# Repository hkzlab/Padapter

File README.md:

# The Padapter, Genesis/MegaDrive gamepad to C64/Amiga adapter

## DISCLAIMER

Any use of this project is **under your own responsibility**.
You will be responsible of checking the correct construction and functionality of your board.
By using this project You will agree that I cannot be held responsible if it will destroy any of your devices, damage your computer, burn down your house or whatever.

## Introduction

This board converts a SEGA MegaDrive/Genesis 3-button gamepad for C64 (and similar)/Amiga use. It is inspired by the [OpenC64MegaDrivePadAdapter](https://github.com/SukkoPera/OpenC64MegaDrivePadAdapter).

All buttons on the gamepad are demultiplexed and usable by the computer, the adapter also provides two switchable mappings to help with games that used the joystick up direction for jumping.

### Ordering the boards

You can order the board for this project at [PCBWay](https://www.pcbway.com/project/shareproject/The_Padapter_6d3f13b7.html) and support me or download 
the gerbers and have them printed wherever you like!!!

Fabrication files are available for both PCBWay and JLCPCB inside the "gerbers" directory. Mind you that I have not yet tested assembly
of this board by either fab, as such you are on your own and you're invited to share your experience and improvements to these files.

## Features

- Small and made with common components
- Maps 3 buttons of the gamepad adapter, allowing their use on both C64 (and similar) and Amiga
- Two switchable button Maps

Amiga and C64 modes can be switched by moving JP1 and JP2:
- Pins 1-2 connected: Amiga Mode
- Pins 2-3 connected: C64 Mode

### Button Maps

Two button maps are available and switchable by flipping SW1 on the board.

They are switchable on the fly.

|              | Mode A   | Mode B   |
| ------------ | -------- | -------- |
| START        | Button 3 | Button 3 |
| A            | Button 3 | Button 2 |
| B            | Button 1 | Button 1 |
| C            | Button 2 | UP       |

## Hardware

The board was designed with [KiCad](https://kicad.org/) EDA.

### Bill of Materials

| Component              | Qty | Type / Value                                            | Notes                                                                |
| ---------------------- | --- | ------------------------------------------------------- | -------------------------------------------------------------------- |
| C1, C2                 |  2  | 10nF/10+V ceramic cap, SMD 0805                         |                                                                      |
| C3 - C15               | 13  | 100nF/10+V ceramic cap, SMD 0805                        |                                                                      |
| D1 - D5                |  5  | 1N4148W SOD-123F diode                                  |                                                                      |
| J1                     |  1  | DSUB-9 Female                                           | Connect toward C64/Amiga, use a connector with solder cups           |
| J2                     |  1  | DSUB-9 Male                                             | Connect toward MegaDrive pad, use a connector with solder cups       |
| JP1, JP2               |  2  | 3 pin 2.54mm headers                                    | Used to select between C64 and Amiga mode                            |
| Q1, Q2                 |  2  | BC847 SOT-23 transistors                                |                                                                      |
| R1, R3, R4, R6         |  4  | 2.2K ohm 0805 resistor                                  |                                                                      |
| R2, R5                 |  2  | 100K ohm 0805 resistor                                  |                                                                      |
| R7 - R9                |  3  | 10K ohm 0805 resistor                                   |                                                                      |
| RN1, RN2               |  2  | 10K resistor pack, 4x0612 (1206)                        |                                                                      |
| SW1                    |  1  | SPDT switch, C&K JS102011SAQN                           |                                                                      |
| U1                     |  1  | 74ACT08 TSSOP-14                                        |                                                                      |
| U2, U4                 |  2  | 74ACT373 SSOP-20                                        |                                                                      |
| U3                     |  1  | 74ACT157 TSSOP-16                                       |                                                                      |
| U5                     |  1  | 74AHC1G04 SOT-353 SC-70 5pin                            |                                                                      |
| 555                    |  1  | A CMOS 555 counter (e.g. LM555) SOIC-8                  |                                                                      |

### 💰 Selling these boards 💰

I you want to contact me about selling this project, you can reach me via email at `0hkzUNDERSCOREprojects6ATposteoDOTnet` after properly fixing the email address by removing the digits and replacing the uppercase words with the proper characters.

**Contacts via other channels will be ignored**, as it means you did not read this document thoroughly.

"Collaborations" will boil down to the following:

- If you wish to produce and share this project at a loss or at cost, go for it. I am only asking for attribution and to let me know via email.
- If you want to do it for profit, let's discuss it. I'll probably settle for a rough 5% of the profit. Importing components is getting more expensive by the day, so this will contribute to me making future projects available for free.
- I will NOT do customer assistance for you or your customers. This is a hobby, not my job.

If this is not ok for you, you're cordially invited to go bother someone else :)

Authorized sellers will be listed in this README. If you find someone selling my boards without being listed here, it means they're stealing other people's work.

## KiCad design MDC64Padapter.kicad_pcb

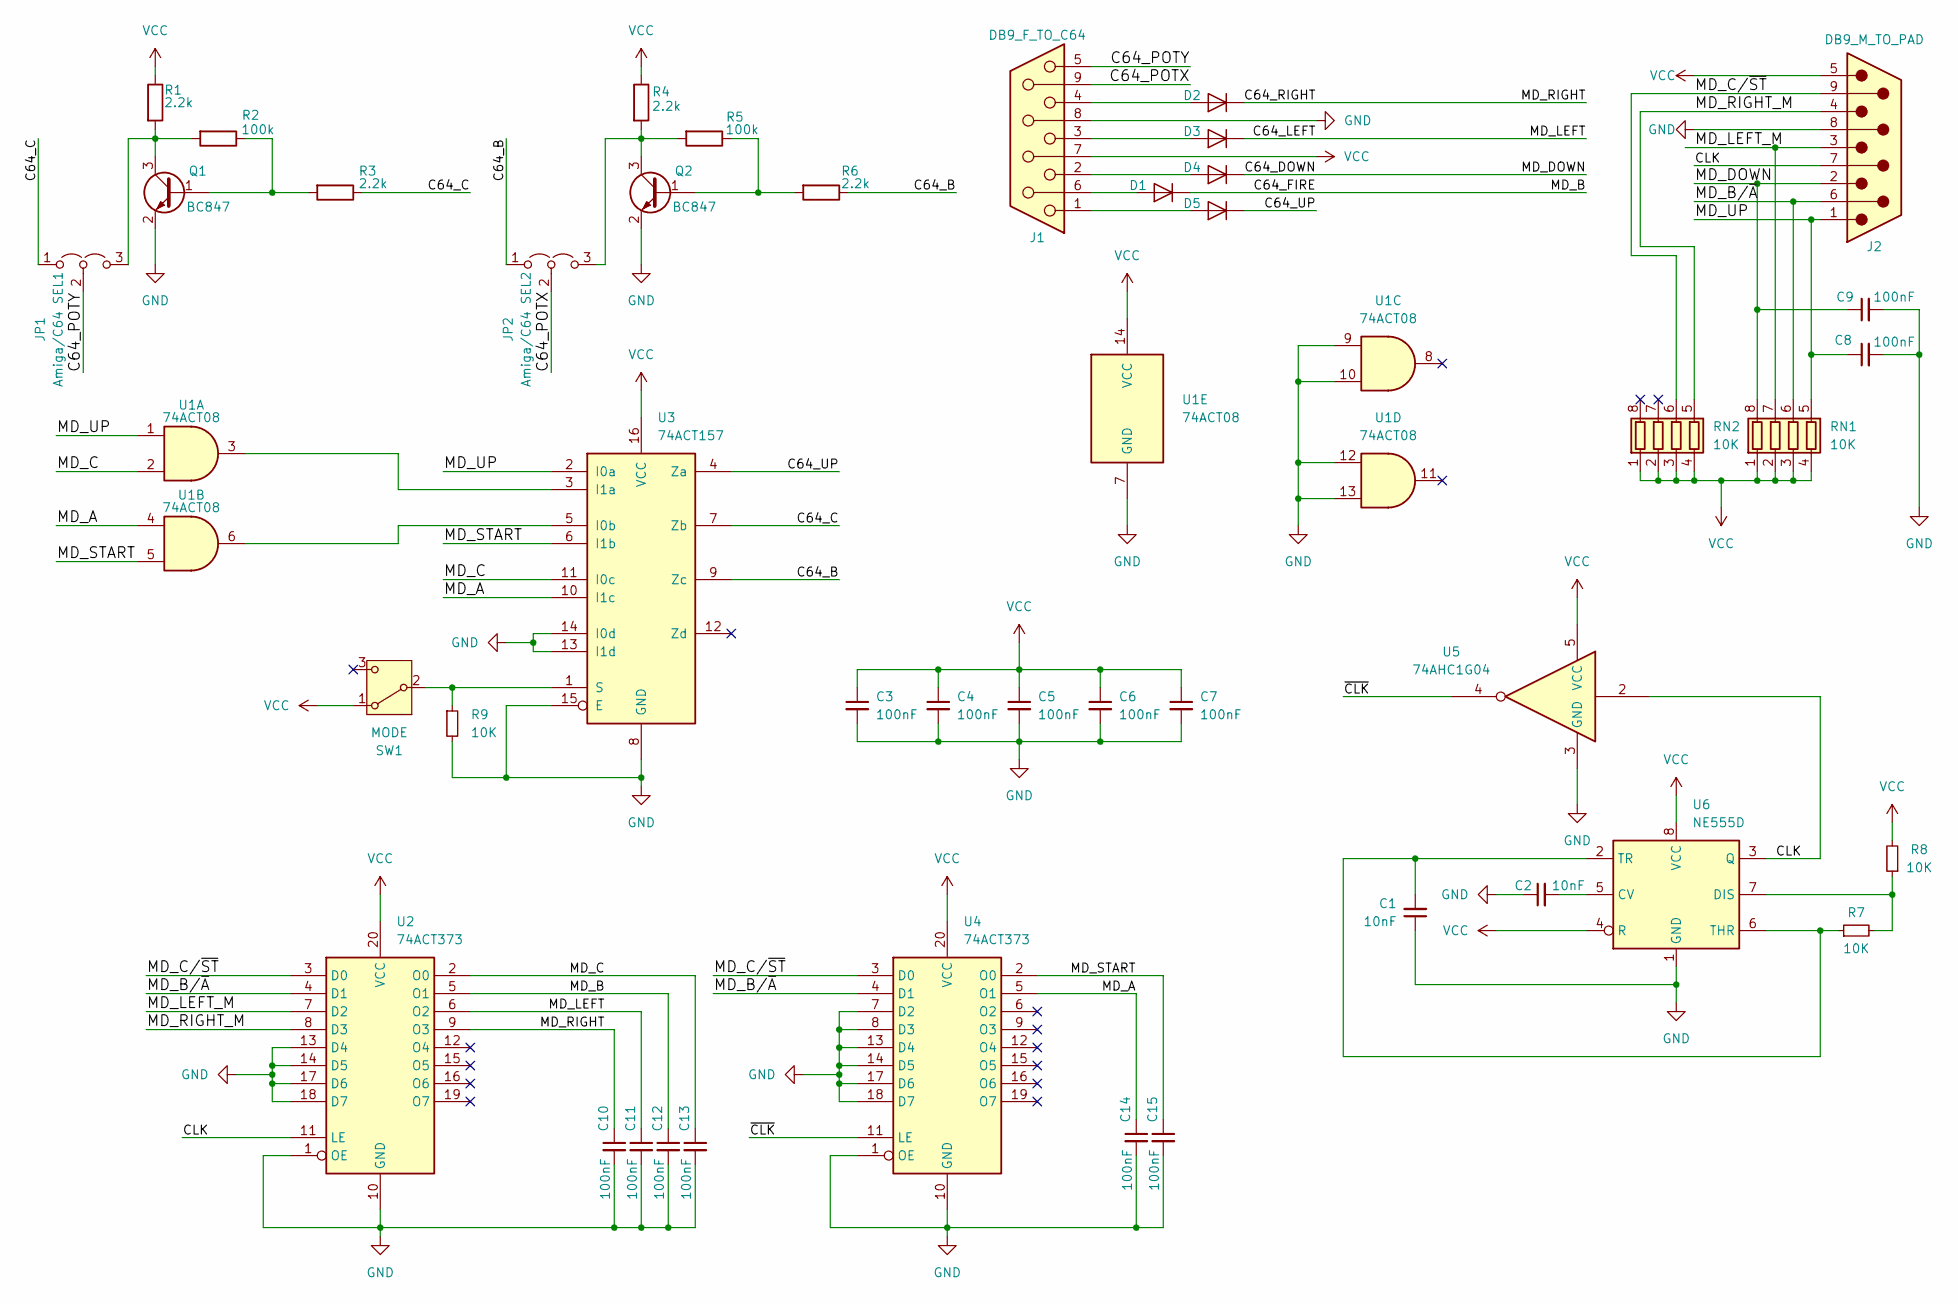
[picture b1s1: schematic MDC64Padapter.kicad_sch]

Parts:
C1, C2: 10nF; C_0805_2012Metric_Pad1.18x1.45mm_HandSolder; LCSC PN C83170
C3, C4, C5, C6, C7, C8, C9, C10, C11, C12, C13, C14, C15: 100nF; C_0805_2012Metric_Pad1.18x1.45mm_HandSolder; LCSC PN C38141
D1, D2, D3, D4, D5: 1N4148; D_SOD-123F; LCSC PN C83528
J1: DB9_F_TO_C64; DSUB-9_Female_EdgeMount_P2.77mm
J2: DB9_M_TO_PAD; DSUB-9_Male_EdgeMount_P2.77mm
JP1: Amiga/C64 SEL1; PinHeader_1x03_P2.54mm_Vertical
JP2: Amiga/C64 SEL2; PinHeader_1x03_P2.54mm_Vertical
Q1, Q2: BC847; SOT-23; LCSC PN C475630
R1, R3, R4, R6: 2.2k; R_0805_2012Metric_Pad1.20x1.40mm_HandSolder; LCSC PN C17520
R2, R5: 100k; R_0805_2012Metric_Pad1.20x1.40mm_HandSolder; LCSC PN C149504
R7, R8, R9: 10K; R_0805_2012Metric_Pad1.20x1.40mm_HandSolder; LCSC PN C17414
RN1, RN2: 10K; R_Array_Convex_4x0612; LCSC PN C840645
SW1: MODE; SW_SPDT_CK_JS102011SAQN; LCSC PN C221660
U1: 74ACT08; TSSOP-14_4.4x5mm_P0.65mm; LCSC PN C238944
U2, U4: 74ACT373; SSOP-20_5.3x7.2mm_P0.65mm; LCSC PN C4989112
U3: 74ACT157; TSSOP-16_4.4x5mm_P0.65mm; LCSC PN C3239134
U5: 74AHC1G04; SOT-353_SC-70-5_Handsoldering; LCSC PN C148197
U6: NE555D; SOIC-8_3.9x4.9mm_P1.27mm; LCSC PN C41431778

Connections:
/C64_B: JP2.1 (A), R6.1, U3.9 (Zc)
/C64_C: JP1.1 (A), R3.1, U3.7 (Zb)
/C64_DOWN: C9.1, D4.1 (K), J2.2, RN1.8 (R1.2)
/C64_FIRE: C12.1, D1.1 (K), U2.5 (O1)
/C64_LEFT: C11.1, D3.1 (K), U2.6 (O2)
/C64_POTX: J1.9, JP2.2 (C)
/C64_POTY: J1.5, JP1.2 (C)
/C64_RIGHT: C10.1, D2.1 (K), U2.9 (O3)
/C64_UP: D5.1 (K), U3.4 (Za)
/CLK: J2.7, U2.11 (LE), U5.2, U6.3 (Q)
/MD_A: C14.1, U1.4, U3.10 (I1c), U4.5 (O1)
/MD_B/~A: J2.6, RN1.6 (R3.2), U2.4 (D1), U4.4 (D1)
/MD_C: C13.1, U1.2, U2.2 (O0), U3.11 (I0c)
/MD_C/~ST: J2.9, RN2.6 (R3.2), U2.3 (D0), U4.3 (D0)
/MD_LEFT_M: J2.3, RN1.7 (R2.2), U2.7 (D2)
/MD_RIGHT_M: J2.4, RN2.5 (R4.2), U2.8 (D3)
/MD_START: C15.1, U1.5, U3.6 (I1b), U4.2 (O0)
/MD_UP: C8.1, J2.1, RN1.5 (R4.2), U1.1, U3.2 (I0a)
/~CLK: U4.11 (LE), U5.4
GND: C1.1, C2.1, C3.2, C4.2, C5.2, C6.2, C7.2, C8.2, C9.2, C10.2, C11.2, C12.2, C13.2, C14.2, C15.2, J1.8, J2.8, Q1.2 (E), Q2.2 (E), R9.2, U1.7 (GND), U1.9, U1.10, U1.12, U1.13, U2.1 (OE), U2.10 (GND), U2.13 (D4), U2.14 (D5), U2.17 (D6), U2.18 (D7), U3.8 (GND), U3.13 (I1d), U3.14 (I0d), U3.15 (E), U4.1 (OE), U4.7 (D2), U4.8 (D3), U4.10 (GND), U4.13 (D4), U4.14 (D5), U4.17 (D6), U4.18 (D7), U5.3 (GND), U6.1 (GND)
unnamed: D1.2 (A), J1.6
unnamed: D2.2 (A), J1.4
unnamed: D3.2 (A), J1.3
unnamed: D4.2 (A), J1.2
unnamed: D5.2 (A), J1.1
unnamed: JP1.3 (B), Q1.3 (C), R1.2, R2.2
unnamed: JP2.3 (B), Q2.3 (C), R4.2, R5.2
unnamed: Q1.1 (B), R2.1, R3.2
unnamed: Q2.1 (B), R5.1, R6.2
unnamed: R9.1, SW1.2 (B), U3.1 (S)
unnamed: U1.6, U3.5 (I0b)
unnamed: U1.3, U3.3 (I1a)
unnamed: C2.2, U6.5 (CV)
unnamed: R7.2, R8.1, U6.7 (DIS)
unnamed: C1.2, R7.1, U6.2 (TR), U6.6 (THR)
VCC: C3.1, C4.1, C5.1, C6.1, C7.1, J1.7, J2.5, R1.1, R4.1, R8.2, RN1.1 (R1.1), RN1.2 (R2.1), RN1.3 (R3.1), RN1.4 (R4.1), RN2.1 (R1.1), RN2.2 (R2.1), RN2.3 (R3.1), RN2.4 (R4.1), SW1.1 (A), U1.14 (VCC), U2.20 (VCC), U3.16 (VCC), U4.20 (VCC), U5.5 (VCC), U6.4 (R), U6.8 (VCC)

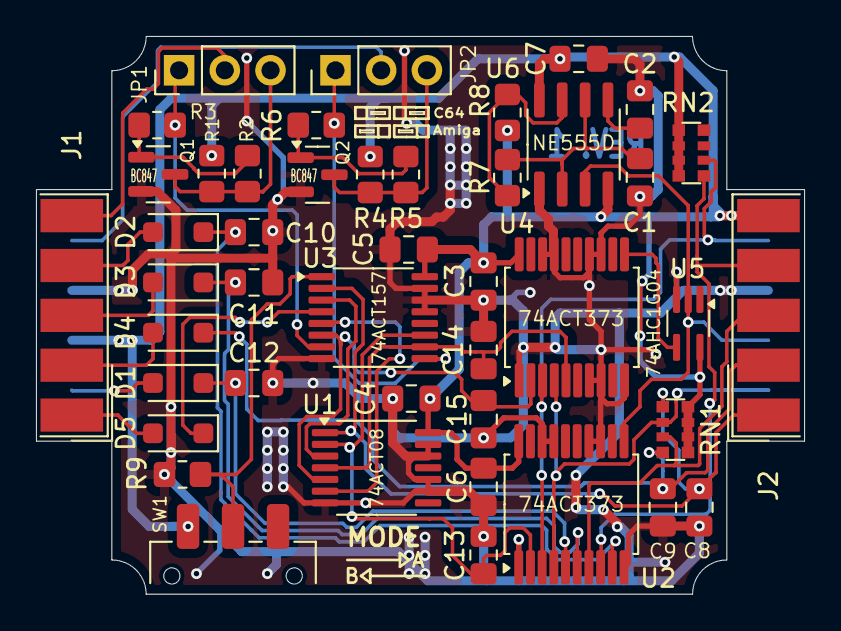
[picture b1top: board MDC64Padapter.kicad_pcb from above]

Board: 2 copper layers, 42.7 x 31.0 mm, 44 parts (0 on the bottom side), 36 nets.

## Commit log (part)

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2025-01-02 First schematic of the padapter
2025-01-02 Use a cmos mux
2025-01-02 Begin placing components on the PCB
2025-01-02 Reorganize pcb a bit
2025-01-02 First PCB design
2025-01-02 Update adapter
2025-01-02 add some silkscreen
2025-01-02 Update PCB
2025-01-02 Reorg
2025-01-02 Add amiga compatibility
2025-01-02 Tweak some traces
2025-01-02 First rev of the board
2025-02-03 Change the silkscreen
2025-02-04 Fix 555 cap/resistor values
2025-02-04 Correct connection mistake
2025-02-04 Additional fix
2025-02-05 Fix c64 up signal traces on PCB
2025-02-05 Add filter caps on up/down direction
2025-02-05 Add filter caps for up/down direction
2025-02-05 Add filtering caps to the outputs of the latches
2025-02-05 Begin reorganizing the board
2025-02-05 Reorganize the board a bit
2025-02-05 Reroute the adapter
2025-02-05 build rev.1 gerbers
2025-02-05 Tweak routing a bit
2025-02-13 Tweak schematic
2025-02-13 Add LCSC PNs
2025-03-25 Update wrong LCSC numbers for two capacitors
2025-03-25 Fixed a part number and add fabrication files for PCBWay and JLCPCB
2025-03-25 Update the README mentioning fabrication files
2025-03-25 Add PCBWay link
2025-09-21 Push last changes for rev. 1
